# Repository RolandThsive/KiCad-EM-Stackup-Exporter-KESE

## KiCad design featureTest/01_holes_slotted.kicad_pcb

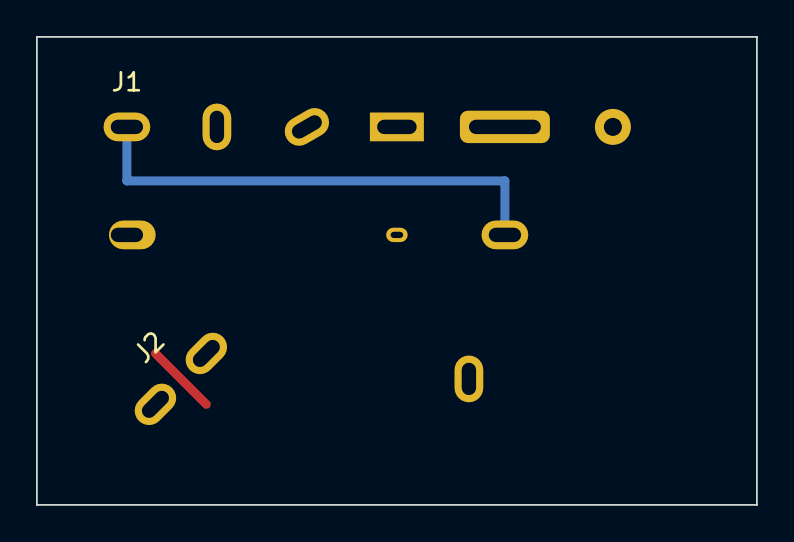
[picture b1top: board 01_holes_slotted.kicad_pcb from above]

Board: 2 copper layers, 40.0 x 26.0 mm, 3 parts (1 on the bottom side), 2 nets.

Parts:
J1: Slots
J2: Slots45
J3: SlotBack

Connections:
SLOT_FP45: J2.1, J2.2
SLOT_H: J1.1, J1.11
